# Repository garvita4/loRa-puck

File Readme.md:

# LoRaPuck 

okay so this is my LoRa board. it's a little 4-layer PCB that sends data through the air with no wifi, no cell towers, no internet, nothing. just radio waves. and LoRa is made for long range, so two of these can talk to each other from kilometers away.

## why i made this

i wanted to know how radio boards actually work. also i wanted to make something cool.....so i made it using the guide https://blueprint.hackclub.com/starter-projects/lora.

## project showcase

## specs

- **PCB size:** 50 mm x 50 mm
- **frequency:** 915 MHz.
- **layers:** 4. top and bottom are for signals, inner 1 is a solid ground plane, inner 2 is the 3.3V plane
- **RF traces:** CPWG (coplanar waveguide with ground) at the width i calculated for 50 ohm, using KiCad's calculator
- **ground pours:** everywhere there's free space, to cut down noise
- **via fences:** i lined the RF section with ground vias and stitched the rest of the board too. noise has nowhere to go
- **header pins:** broken out so you can plug in your own sensors
- **the numbers:** 237 pads, 84 vias, 591 track segments, 74 nets, 0 unrouted. DRC is clean except for the USB footprint warnings (those are normal, i checked)

## how it works

- You plug it in via USB-C. This powers the board and lets you flash your code to the RP2040 microcontroller, which acts as the brain of the whole thing.

- When the RP2040 wants to send a message, it talks to the SX1262 LoRa chip.

- The LoRa chip blasts that data out as radio waves through the antenna (which sticks right out of the 7mm porthole I designed into the top of the case).

- You get a portable little node that can bounce short messages or sensor data over miles without needing Wi-Fi, Bluetooth, or a cell tower.

## schematic

i split it into three blocks so it's easier to read: USB-C, the RP2040, and the RF device.

## PCB layout

i laid out the MCU, radio and USB as their own little sections first, then put them together, keeping the RF part as far from the noisy stuff as i could. decoupling caps are right next to the pins they belong to, and the inductor on the radio's switching regulator got fat traces because it switches fast.

## the case

i designed the case in Fusion 360. it's two parts you can 3D print: a bottom shell with four posts for the PCB to sit on, and a lid with a Mickey-head inlay on top (because why not). there are three vent slots on the side and a hole for the USB-C port.

## firmware

the firmware is vibecoded yet...once the hardware part is done,i'll work on it.

## BOM
| Part | Description | Qty | Unit Cost | Total Cost | Vendor |
| ---- | ----------- | --- | --------- | ---------- | ------ |
| PCB | 4-layer PCB | 1 | $20.10 | $20.10 | [zbotic.in](https://zbotic.in/pcb-manufacturing/) |
| SX1262IMLTRT | LoRa RF transceiver | 1 | $5.52 | $5.52 | [robu.in](https://robu.in/product/sx1262imltrt-semitech-300kbps-general-purposeism1ghz-spi-qfn-24-ep4x4-rf-transceiver-ics-rohs/) |
| RP2040 | Main microcontroller | 1 | $0.68 | $0.68 | [robu.in](https://robu.in/product/raspberry-pi-rp2040/) |
| PE4259 | RF antenna path switch | 1 | $0.60 | $0.60 | [sharvi](https://sharvielectronics.com/product/4259-63-spdt-high-power-ultracmos-10mhz-to-3-0ghz-rf-switch-ic-sc-70-6-package/) |
| W25Q128JVS | 128-Mbit SPI flash memory | 1 | $2.02 | $2.02 | [sharvi](https://sharvielectronics.com/product/w25q128-flash-chip-128mbit-16mb-soic-8-package/) |
| AP2112K-3.3 | 3.3 V voltage regulator | 1 | $0.22 | $0.22 | [sharvi](https://sharvielectronics.com/product/ap2112k-3-3trg1-3-3v-600ma-ldo-voltage-regulator-sot-25-5-package/) |
| USB-C receptacle (GCT USB4105 family) | USB power and USB 2.0 data connection | 1 | $0.21 | $0.21 | [sharvi](https://sharvielectronics.com/product/16-pin-c-type-usb-connector-smd-package/) |
| PTS636Sx25SMTRLFS family tactile switch | BOOTSEL and RESET buttons | 4 | $0.49 | $1.96 | [robu.in](https://robu.in/product/pts636sk25smtrlfs-ck-rectangle-button-50ma-standing-paste-spst-normally-open-250gf-12v-tactile-switches-rohs/) |
| Antenna | LoRa RF transmission and reception | 1 | $0.84 | $0.84 | [robu.in](https://robu.in/product/lora-antenna-915mhz/) |
| 32 MHz SMD Crystal | SX1262 RF reference clock | 2 | $0.20 | $0.40 | [sharvi](https://sharvielectronics.com/product/32mhz-10pf-%c2%b110ppm-tolerance-r2520-32-000-10-f-1010-tr-ns8-smd-crystal-2-50mmx2mm-package/) |
| Case | 3D printed body | 1 | $32.00 | $32.00 | [printlegion](https://printlegion.hackclub.com/) |
| Tax & shipping | For the whole order | - | - | $0.00 | - |
| **Grand Total** | | | | **$64.55** | |

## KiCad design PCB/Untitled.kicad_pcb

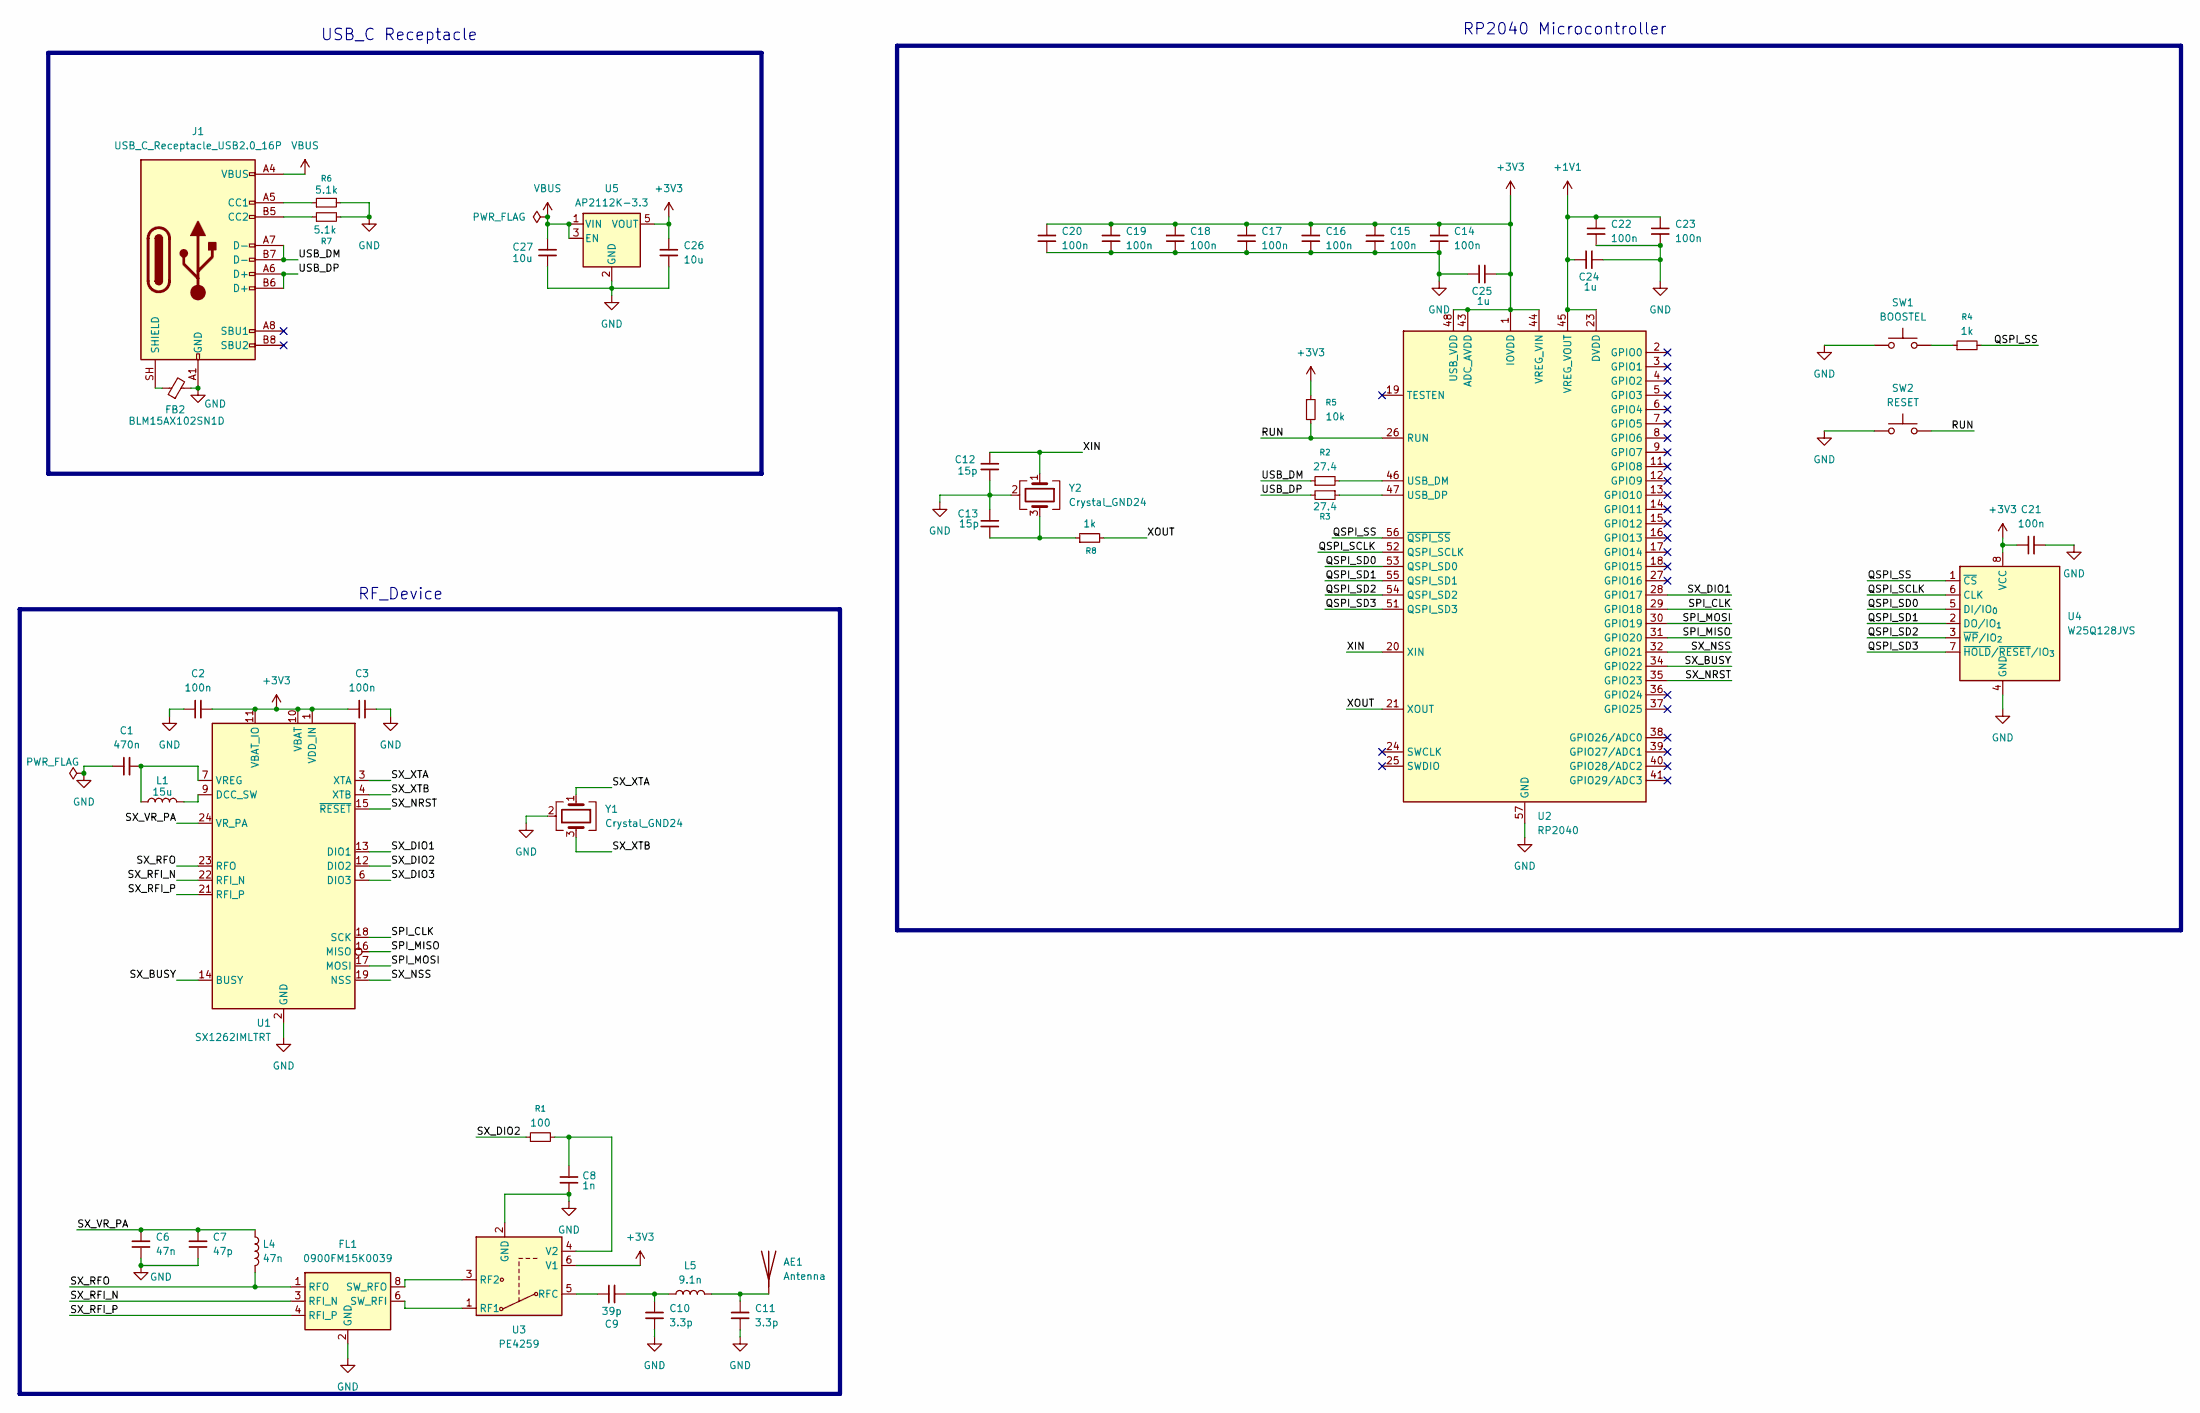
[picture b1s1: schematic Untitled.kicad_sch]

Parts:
AE1: Antenna; PinSocket_1x01_P2.54mm_Vertical
C1: 470n; C_0402_1005Metric
C2, C3, C14, C15, C16, C17, C18, C19, C20, C21, C22, C23: 100n; C_0402_1005Metric
C6: 47n; C_0402_1005Metric
C7: 47p; C_0402_1005Metric
C8: 1n; C_0402_1005Metric
C9: 39p; C_0402_1005Metric
C10, C11: 3.3p; C_0402_1005Metric
C12, C13: 15p; C_0402_1005Metric
C24, C25: 1u; C_0402_1005Metric
C26, C27: 10u; C_0402_1005Metric
FB2: BLM15AX102SN1D; L_0402_1005Metric
FL1: 0900FM15K0039; Balun_Johanson_0900FM15K0039
J1: USB_C_Receptacle_USB2.0_16P; USB_C_Receptacle_GCT_USB4105-xx-A_16P_TopMnt_Horizontal
L1: 15u; L_0402_1005Metric
L4: 47n; L_0402_1005Metric
L5: 9.1n; L_0402_1005Metric
R1: 100; R_0402_1005Metric
R2, R3: 27.4; R_0402_1005Metric
R4, R8: 1k; R_0402_1005Metric
R5: 10k; R_0402_1005Metric
R6, R7: 5.1k; R_0402_1005Metric
SW1: BOOSTEL; SW_Tactile_SPST_NO_Straight_CK_PTS636Sx25SMTRLFS
SW2: RESET; SW_Tactile_SPST_NO_Straight_CK_PTS636Sx25SMTRLFS
U1: SX1262IMLTRT; HVQFN-24-1EP_4x4mm_P0.5mm_EP2.6x2.6mm
U2: RP2040; QFN-56-1EP_7x7mm_P0.4mm_EP3.2x3.2mm
U3: PE4259; SOT-363_SC-70-6
U4: W25Q128JVS; SOIC-8_5.3x5.3mm_P1.27mm
U5: AP2112K-3.3; SOT-23-5
Y1: Crystal_GND24; Crystal_SMD_3225-4Pin_3.2x2.5mm
Y2: Crystal_GND24; Crystal_SMD_Abracon_ABM8G-4Pin_3.2x2.5mm

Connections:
+1V1: C22.1, C23.1, C24.1, U2.23 (DVDD), U2.45 (VREG_VOUT), U2.50 (DVDD)
+3V3: C2.2, C3.1, C14.1, C15.1, C16.1, C17.1, C18.1, C19.1, C20.1, C21.1, C25.2, C26.1, R5.1, U1.1 (VDD_IN), U1.10 (VBAT), U1.11 (VBAT_IO), U2.1 (IOVDD), U2.10 (IOVDD), U2.22 (IOVDD), U2.33 (IOVDD), U2.42 (IOVDD), U2.43 (ADC_AVDD), U2.44 (VREG_VIN), U2.48 (USB_VDD), U2.49 (IOVDD), U3.6 (V1), U4.8 (VCC), U5.5 (VOUT)
/QSPI_SCLK: U2.52 (QSPI_SCLK), U4.6 (CLK)
/QSPI_SD0: U2.53 (QSPI_SD0), U4.5 (DI/IO_{0})
/QSPI_SD1: U2.55 (QSPI_SD1), U4.2 (DO/IO_{1})
/QSPI_SD2: U2.54 (QSPI_SD2), U4.3 (~WP/IO_{2})
/QSPI_SD3: U2.51 (QSPI_SD3), U4.7 (~HOLD/~RESET/IO_{3})
/QSPI_SS: R4.2, U2.56 (~QSPI_SS), U4.1 (~CS)
/RUN: R5.2, SW2.2, U2.26 (RUN)
/SPI_CLK: U1.18 (SCK), U2.29 (GPIO18)
/SPI_MISO: U1.16 (MISO), U2.31 (GPIO20)
/SPI_MOSI: U1.17 (MOSI), U2.30 (GPIO19)
/SX_BUSY: U1.14 (BUSY), U2.34 (GPIO22)
/SX_DIO1: U1.13 (DIO1), U2.28 (GPIO17)
/SX_DIO2: R1.1, U1.12 (DIO2)
/SX_DIO3: U1.6 (DIO3)
/SX_NRST: U1.15 (~RESET), U2.35 (GPIO23)
/SX_NSS: U1.19 (NSS), U2.32 (GPIO21)
/SX_RFI_N: FL1.3 (RFI_N), U1.22 (RFI_N)
/SX_RFI_P: FL1.4 (RFI_P), U1.21 (RFI_P)
/SX_RFO: FL1.1 (RFO), L4.2, U1.23 (RFO)
/SX_VR_PA: C6.1, C7.1, L4.1, U1.24 (VR_PA)
/SX_XTA: U1.3 (XTA), Y1.1
/SX_XTB: U1.4 (XTB), Y1.3
/USB_DM: J1.A7 (D-), J1.B7 (D-), R2.1
/USB_DP: J1.A6 (D+), J1.B6 (D+), R3.2
/XIN: C12.1, U2.20 (XIN), Y2.1
/XOUT: R8.2, U2.21 (XOUT)
GND: C1.1, C2.1, C3.2, C6.2, C7.2, C8.2, C10.2, C11.2, C12.2, C13.1, C14.2, C15.2, C16.2, C17.2, C18.2, C19.2, C20.2, C21.2, C22.2, C23.2, C24.2, C25.1, C26.2, C27.1, FB2.2, FL1.2 (GND), FL1.5 (GND), FL1.7 (GND), FL1.9 (GND), FL1.10 (GND), J1.A1 (GND), J1.A12 (GND), J1.B1 (GND), J1.B12 (GND), R6.2, R7.2, SW1.1, SW2.1, U1.2 (GND), U1.5 (GND), U1.8 (GND), U1.20 (GND), U1.25 (GND), U2.57 (GND), U3.2 (GND), U4.4 (GND), U5.2 (GND), Y1.2 (G), Y1.4 (G), Y2.2 (G), Y2.4 (G)
unnamed: AE1.1 (A_1), C11.1, L5.2
unnamed: C9.2, C10.1, L5.1
unnamed: C13.2, R8.1, Y2.3
unnamed: FL1.6 (SW_RFI), U3.1 (RF1)
unnamed: FL1.8 (SW_RFO), U3.3 (RF2)
unnamed: J1.A5 (CC1), R6.1
unnamed: J1.B5 (CC2), R7.1
unnamed: FB2.1, J1.SH (SHIELD)
unnamed: R4.1, SW1.2
unnamed: L1.2, U1.9 (DCC_SW)
unnamed: C1.2, L1.1, U1.7 (VREG)
unnamed: R2.2, U2.46 (USB_DM)
unnamed: R3.1, U2.47 (USB_DP)
unnamed: C9.1, U3.5 (RFC)
unnamed: C8.1, R1.2, U3.4 (V2)
VBUS: C27.2, J1.A4 (VBUS), J1.A9 (VBUS), J1.B4 (VBUS), J1.B9 (VBUS), U5.1 (VIN), U5.3 (EN)

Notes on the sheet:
RF_Device
RP2040 Microcontroller
USB_C Receptacle

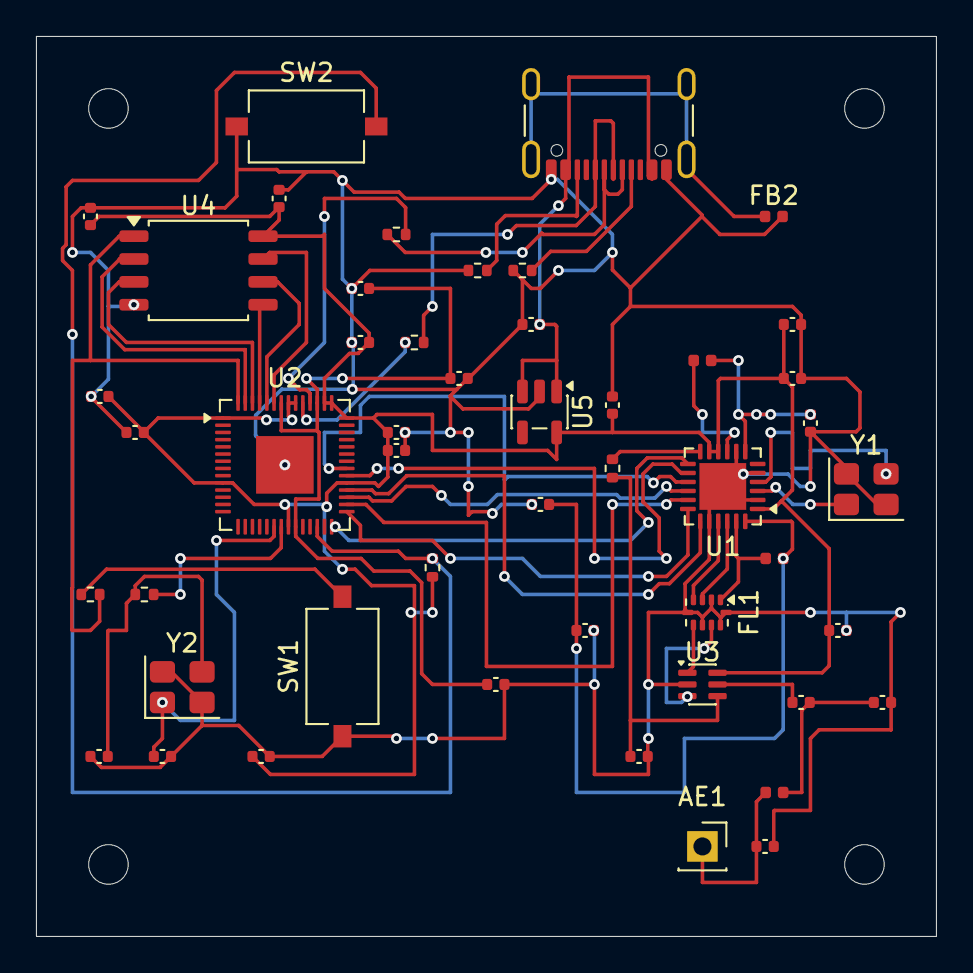
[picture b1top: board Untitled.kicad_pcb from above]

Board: 4 copper layers, 50.0 x 50.0 mm, 49 parts (0 on the bottom side), 44 nets.

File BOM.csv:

Part,Description,Qty,Unit Cost,Total Cost,Vendor
PCB,4-layer PCB,1,$20.10,$20.10,zbotic.in
SX1262IMLTRT,LoRa RF transceiver,1,$5.52,$5.52,robu.in
RP2040,Main microcontroller,1,$0.68,$0.68,robu.in
PE4259,RF antenna path switch,1,$0.60,$0.60,sharvi
W25Q128JVS,128-Mbit SPI flash memory,1,$2.02,$2.02,sharvi
AP2112K-3.3,3.3 V voltage regulator,1,$0.22,$0.22,sharvi
USB-C receptacle (GCT USB4105 family),USB power and USB 2.0 data connection,1,$0.21,$0.21,sharvi
PTS636Sx25SMTRLFS family tactile switch,BOOTSEL and RESET buttons,4,$0.49,$1.96,robu.in
Antenna,LoRa RF transmission and reception,1,$0.84,$0.84,robu.in
32 MHz SMD Crystal,SX1262 RF reference clock,2,$0.20,$0.40,sharvi
Case,3D printed body,1,$32.00,$32.00,printlegion
Tax & shipping,For the whole order,-,-,$0.00,-
Grand Total,,,,$64.55,
